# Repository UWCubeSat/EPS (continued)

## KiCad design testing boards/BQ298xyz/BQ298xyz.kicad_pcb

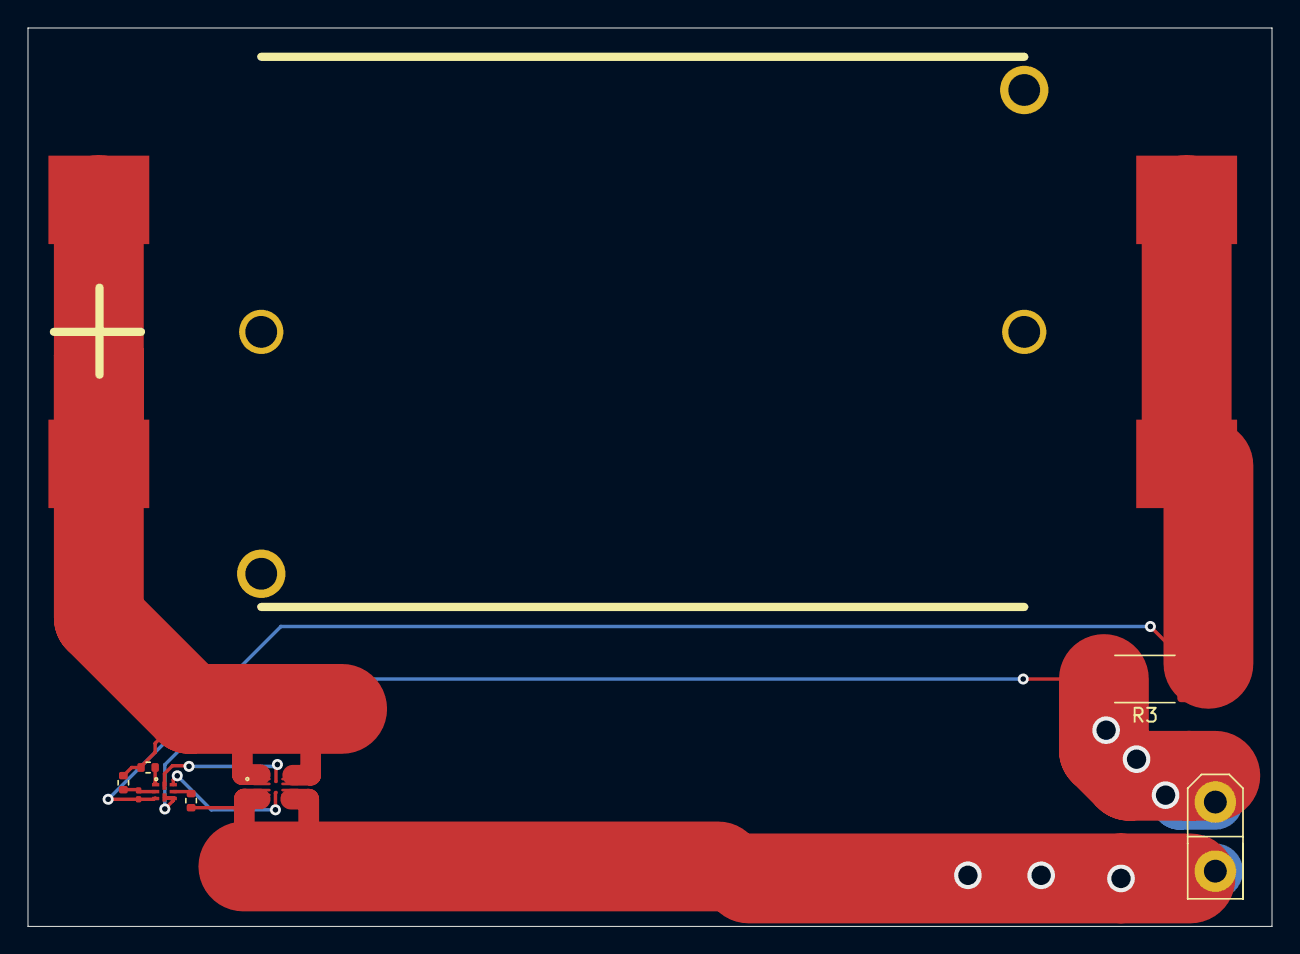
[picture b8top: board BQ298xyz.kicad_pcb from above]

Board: 2 copper layers, 90.0 x 65.0 mm, 9 parts (0 on the bottom side), 9 nets.

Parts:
C1: 0.1uF; C_0201_0603Metric
J1: XT30
R1: 100; R_0402_1005Metric
R2: 20; R_0402_1005Metric
R3: 1mOhm; R_2512_6332Metric
R4: 1k; R_0402_1005Metric
U1: 1048-2S-18650-Holder; 1048-2S-18650
U2: BQ298xyz
U3: EFC2K103NUZTDG

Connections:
/BATT+: R1.1, R2.1, U1.1, U1.2, U3.1
/BATT-: C1.2, R3.1, U1.3, U1.4, U2.3
/CHG: U2.8, U3.3
/PACK+: J1.1, R4.1, U3.2
/PACK-: J1.2, R3.2, U2.4, U2.5
unnamed: C1.1, R1.2, U2.2
unnamed: R2.2, U2.1
unnamed: R4.2, U2.6
unnamed: U2.7, U3.4

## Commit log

2021-04-20 First Version EPS Schematic
    Unfinished EPS schematic, more details/finished version hopefully soon to come
2021-04-27 V1 EPS schematic
    Finished schematic:
    Separated battery, solar, and power monitoring/regulation into different boards.
    Added expansion connectors for more power zones/solar panels
    Added current limiting/short circuit protection
2021-05-25 Maybe Final? PCB Design
    Put everything back on a single board for simplicity after considering that all the connectors between boards would probably make a pretty bad rats nest. Immediately had regrets about this decision a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
    This design just barely fits within the size constraints, but I am worried about some very long signal traces and if the 3mm power traces and the very segmented ground plane will be able to handle the
2021-06-19 Finalizing stuff
    Replaced some out of stock parts, fixed some mistakes
2021-10-22 created README.md
    linked to EPS wiki page, can anyone add additional documentation here?
2021-11-21 Created testing boards folder
    Created folder for all of the boards to test specific chips, and added the INA219B breakout board and the TPS2595x1 breakout board
2021-11-29 BQ25798 Breakout Board Added
    Added the breakout board for the BQ25798 1-4S battery charging circuit
2021-12-09 Added More Breakout Boards
2021-12-09 Moved test-boards folder to eps folder
2021-12-09 Moved folder back
2021-12-10 Finished Battery Protection Board
2022-05-17 Did work
    Finished a board, maybe forgot to commit some a while ago?
